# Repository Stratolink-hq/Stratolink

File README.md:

[stratolink.org](https://stratolink.org)

An open source pico balloon network. This repository contains the payload hardware, firmware, website, and flight models. Follow the [docs](https://stratolink.org/docs/getting-started) to build a payload, prepare a balloon, and register it on the [dashboard](https://stratolink.org/dashboard).

## Repository

```text
hardware/    KiCad schematics, PCB layouts, component libraries, and assembly files
firmware/    STM32WLE5 firmware, PlatformIO configuration, and host tests
web/         Website, public docs, dashboard, APIs, and forecast worker
supabase/    Database migrations and permission checks
simulation/  Balloon trajectories, buoyancy, and fleet coverage models
analysis/    Antenna, radio, power, and flight studies; bench diagnostics
docs/        Engineering notes for flight qualification and forecasting
scripts/     Sticker layout tool
assets/      Original project artwork and simulation media
```

## Firmware

Install [PlatformIO](https://platformio.org/install/cli). From the repository root:

```sh
cd firmware
cp include/secrets.h.example include/secrets.h
```

Fill in your regional TTN credentials, then build the flight environment:

```sh
pio run -e stratolink
```

Upload through J-Link over SWD:

```sh
pio run -e stratolink --target upload
```

Use the firmware revision that matches your board. [Hardware setup](https://stratolink.org/docs/hardware) covers assembly and programming; [firmware/README.md](firmware/README.md) covers configuration and host checks.

## Website

Use Node 22. From the repository root:

```sh
cd web
cp .env.example .env.local
ONNXRUNTIME_NODE_INSTALL=skip npm ci
npm run dev
```

Set the values in `.env.local` as described in [web/README.md](web/README.md). Run `npm run verify` before submitting website changes. Deployment and backend setup are documented there.

---

- [Fork this repository](https://github.com/Stratolink-hq/Stratolink/fork)
- [Watch this repo](https://github.com/Stratolink-hq/Stratolink/subscription)
- [Create issue](https://github.com/Stratolink-hq/Stratolink/issues/new)

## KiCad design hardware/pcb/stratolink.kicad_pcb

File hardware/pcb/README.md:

# Stratolink hardware v1.1 pilot

Current status, 8 November 2026: **corrected pilot layout verified; replacement cart saved and reviewed**. The cart contains PCB **Y28-2680969A** and PCBA **SMT026110862453-2680969A**, with all 57 fitted identities, sides and selection checkboxes verified. No replacement order has been submitted or paid, and manufacturing has not been approved. Cancellation of Y27-2680969A / SMT026110264457_Y27 remains requested but unconfirmed. See the [replacement review](../../analysis/v1_1_resubmit_20261108/README.md). The circuit remains unchanged. Layout changes are local clearance corrections; R1 procurement metadata is also updated in the PCB and schematic.

Open [stratolink.kicad_pro](stratolink.kicad_pro) in KiCad 10. The canonical project lives in `hardware/pcb` on `alpha/hardware-v1.1`; Git retains the flown v1. Keep `lib/`, `3d/`, `sym-lib-table` and `fp-lib-table` together. Board-specific footprints retain reviewed pad geometry and mask/paste settings. Do not replace them wholesale with stock footprints. All 68 embedded footprints match their updated local library pad geometry and model attachments; all 63 model attachments resolve with the project assets and KiCad 10 standard models.

The pilot retains the **0.40 mm, two-layer board, ENIG, green solder mask on both faces, no silkscreen and tented ordinary vias**. It uses one radio, the existing GNSS/pressure/IMU parts and the flat rear capacitor. The plan is **five fabricated boards, three assembled**, followed by physical qualification before a larger batch. Source and output hashes belong to the [current review](../../analysis/v1_1_resubmit_20261108/README.md) and [manufacturing manifest](../gerbers/v1.1-resubmit-20261108/manifest.json); use matching files together.

## Current board and assembly

| Area | Configuration |
|---|---|
| GNSS | AE2 at **(59.38, 33.13) mm**, with the **48 mm wire upward** from the top-left feed. Retain the engineer's placement and reviewed ground reference. |
| LoRa | Straight enameled wire downward from AE1. Reference cuts from the feed: **82 mm at 915 MHz**, 86 mm at 868 MHz or 83 mm compromise. |
| Precision temperature | Corrected **TMP117AIYBGR C2871893** ball map at U5, address 0x48. Native placement is now 180°. |
| Microphone | MK1/R20/C13, their dedicated routing and acoustic opening removed; PB3/PB4 unused. |
| Solar mounting | Two **1.0 × 2.0 mm open unplated notches**, upper-bank GND lands on both faces, and separate lower **0.70 mm positive wire holes**. Panels stay parallel. |
| Suspension | **2.0 mm plated holes / 3.2 mm GND rings**, for the triangular string bridle. |
| Programming | J3/J4 ordinary PTH contacts: 1 mm pitch, 0.50 mm holes, 0.88 mm front lands, **1.20 × 0.88 mm rear lands** offset 0.12 mm inward. No castellations. |
| Capacitor | C5 remains the flat hand-fitted rear part, now at **(64.875, 66.007) mm**, native 180°. Its enlarged courtyard is retained in the library. |
| Cell balancing | U8 **TLV8801DBVT** and R24/R25/R26/C22 retained. U8 is now on the **front at native 180°**. |
| Mask | U1 perimeter lands use native **+0.04 mm** mask expansion; U4 and L2 use **+0.05 mm**. Copper and paste geometry are preserved. |

The [mechanical review](../../analysis/v1_1_engineer_review_20261015/mechanics/README.md) includes full assembly, front and rear native renders. The nominal GNSS wire clears the modeled solar assembly by **20.54 mm**. A triangular bridle can cross its XY projection, so keep the actual string behind the wire with space for motion. C5's maximum case clears the board edge by **2.306 mm**, AE1's rear copper land by **0.696 mm** and the nearest Tag-Connect hole by **0.920 mm**. These distances exclude hand-placement error, solder and insulation. The solar film bend, terminal thickness and wire diameter remain nominal model assumptions.

## UV circuit and pilot population

U6 is **ams AS7331-AQFM C20482877**, with separate UVA/UVB/UVC channels, 3.3 V supplies and I²C address **0x74**. C14 and C23 are **100 nF CL05B104KO5NNNC C1525**. R27 is **3.3 MΩ, ±0.1%, ±25 ppm/K MCU0805MD3304BP500 C4313228**. READY is unconnected; SYN and the address inputs are grounded for polled command-mode operation. Current positions and orientations are recorded in the native board and generated placement files, replacing earlier placement notes.

The native design contains the complete circuit. Initial automated assembly **omits U6 only**, retaining **C14, C23 and R27**. Its BOM/CPL omit U6, and its stencil removes exactly the **16 U6 paste apertures**. Full-design paste remains separate for a later reviewed population. U6 is drawn in the full assembly renders but is absent from the three pilot assemblies. [Circuit and sourcing record](../../analysis/v1_1_release_20261012/as7331/README.md).

Build **`platformio run -e stratolink_v1_1_uv_dnp`** from `firmware/` for these pilots. It leaves PB3/PB4 quiet, makes no optical I²C requests and reports UV/lux unavailable. The older `stratolink_v1_1` target expects LTR390. A populated AS7331 has **no supported flight target yet** and requires its own validated driver, power-down behavior and raw multiband telemetry. [Firmware verification](../../analysis/v1_1_release_20261012/as7331/firmware/README.md).

AS7331 supports an experimental estimate of the **ozone column above the balloon**, not calibrated concentration directly. It has no visible-light ALS channel. Its −40…85 °C operating range needs actual die-temperature verification. The manufacturer recommends incidence within ±10° and warns that visible/IR leakage can overwhelm weak UV signals. Angle control, spectral filtering, calibration and low-pressure/thermal qualification remain necessary. U6-absent pilots produce no UV or ozone data. [Primary-source requirements](../../analysis/v1_1_release_20261012/as7331/review/requirements.md).

## Electrical identities and qualification

U5's map is **A1 SDA, A2 SCL, B1 +3.3 V, B2 GND, C1 GND, C2 grounded ALERT**. The AI grade is specified to ±0.2 °C over −40…100 °C and ±0.25 °C over −55…125 °C under its stated conditions. Sunlight and board conduction add ambient-air error. Exact retained identities include **RAK3172-8-SM-NI C5452091** at U2, **RC0402FR-073M65L C477700** at R4 and **PESD5V0U1BB C5272735** at D1/D3. [Identity review](../../analysis/v1_1_release_20261012/identities/README.md).

R1 is **7.50 MΩ UNI-ROYAL 0402WGF7504TCE C423135**, with R2 at 4.22 MΩ, for a nominal **5.041 V** charge ceiling. The stock-driven substitution preserves ±1% tolerance, ±100 ppm/K, 50 V, 62.5 mW and the −55…155 °C operating range, with no footprint or routing change. See the [R1 sourcing review](../../analysis/v1_1_resubmit_20261108/r1-sourcing.md). C5 is **DMF4B5R5G105M3DTA0**: pad 1 positive, pad 2 negative, pad 3 **SC_MID**, not ground. U8 feedback joins the output to its inverting input **before R26**; R26 connects to the midpoint. R24/R25 are 4.75 MΩ, R26 is 22 Ω and C22 is 100 nF. C5 is fitted after reflow and cleaning using its secondary soldering process. [Power circuit review](../../analysis/v1_1_release_20261012/power/README.md).

Charge plateau, both cell voltages, midpoint stability, cold leakage/ESR, dark current and sunrise recovery require measurement. **Cold panel Voc/current and BQ25570 input-voltage/input-power limits remain unresolved physical bounds.** CAD cannot qualify them.

The SWD mapping remains the standard RAK3172 mapping. Use a receive-only adapter for passive J4 UART observation; an adapter transmitter can contend with the GNSS transmitter. Keep the 4.7 kΩ I²C pull-ups pending a measured 300 ns rise-time check. C8/C21 remain. [Digital review](../../analysis/v1_1_peer_review_20261014/digital/README.md), [bypass review](../../analysis/v1_1_peer_review_20261014/power/README.md).

## Manufacturing review

Enabled checks use the reviewed **0.10 mm copper process floor, 0.15 mm general clearance target and 0.20 mm ordinary routed-edge minimum**, with named fine-pitch/contact exceptions. The two intended ERC exclusions are U5 grounded ALERT and U7 SA0. Actual mask Gerbers for the repaired U1/U4/L2 apertures meet **0.09 mm aperture-to-foreign-copper** and **0.10 mm mask-web** checks. Solar polarity symbols are copper with mask openings; native silkscreen artwork count is zero. These checks do not establish controlled impedance, measured RF gain or factory CAM approval.

The package contains **58 full-design / 57 pilot automatic-assembly references**, **30 pilot part groups** and **11 manual/DNP exclusions**. J1/J2/J20 lost their exclude-position flags in the incoming board. The final PCB and schematic restore them; the generator also retains explicit manual exclusions. [BOM, CPL and fabrication package](../gerbers/v1.1-resubmit-20261108/README.md).

**The replacement cart preview has been reviewed; its later factory production files still require review.** The retained supplier CPL conventions are **U1 bottom 270°, U5 top 180° and U8 top 90°**. In a north-up, bottom-facing view, U1 pin 1 is **upper-left beside C4/L1** in the new preview, matching the corrected physical orientation. All seven fitted IC indices were checked. A CSV angle alone does not establish orientation. U6 is omitted. See the [replacement review](../../analysis/v1_1_resubmit_20261108/README.md).

The October packages and Y24/Y26 carts are historical. Y27's PCB production file was approved November 6, but the later assembly review found the body-clearance problem. That approval does not authorize the replacement. Use its new BOM, CPL and Gerbers together and review JLC's new manufacturing and placement files.
- [Fabrication and manual assembly instructions](FABRICATION.md)
- [v1.1 / v2 checklist](TODO.md)
- [Current replacement review and change ledger](../../analysis/v1_1_resubmit_20261108/README.md)
- [October engineer reroute baseline](../../analysis/v1_1_engineer_review_20261015/README.md)
- [Pilot acceptance procedure](../../analysis/v1_1_release_20261012/pilot-acceptance.md)
- [Solar 3D model assumptions](3d/solar/README.md)

Historical analysis files retain earlier placements and supplier previews. Use the current review and package manifest to identify this board.

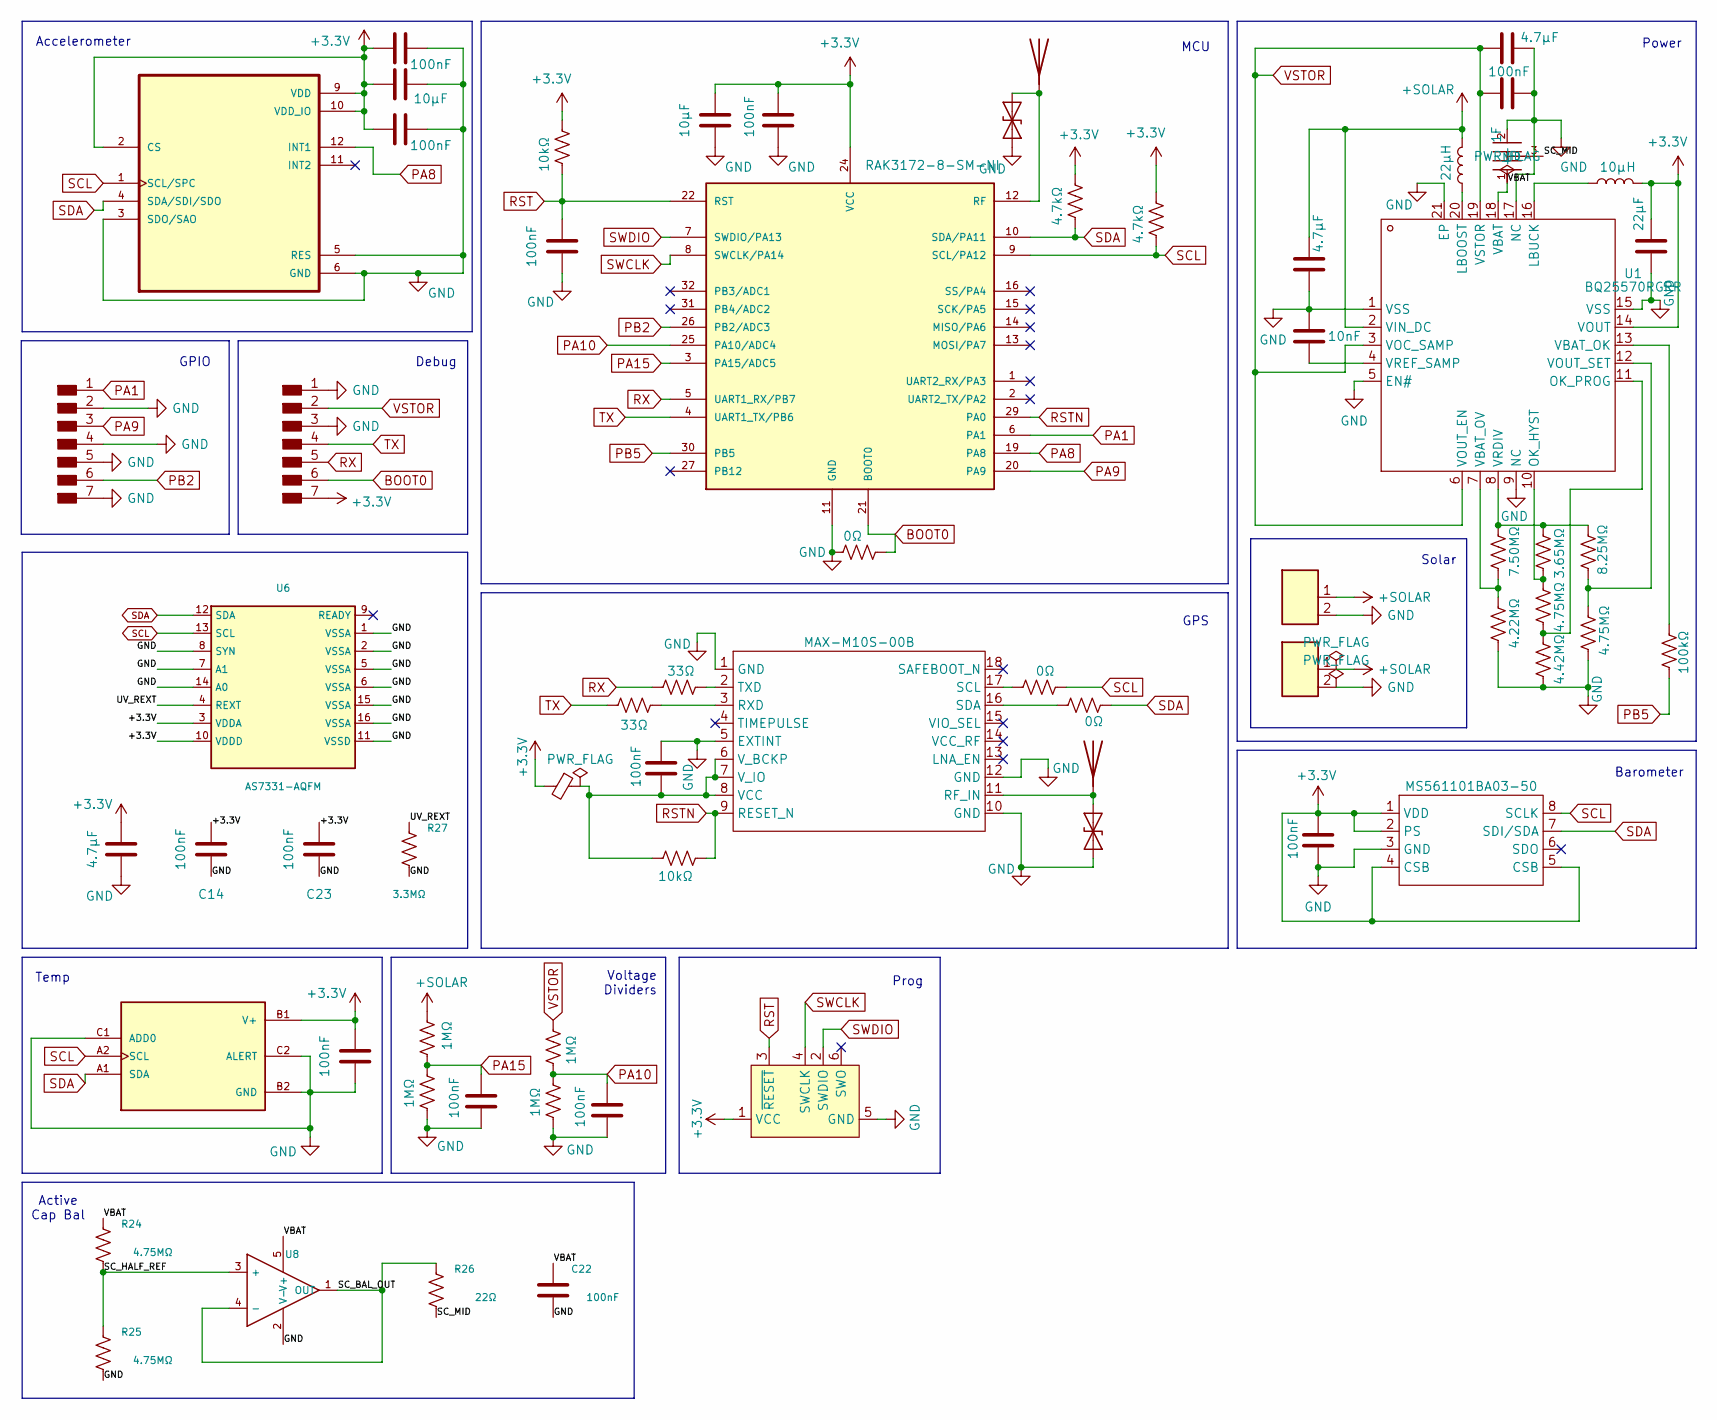
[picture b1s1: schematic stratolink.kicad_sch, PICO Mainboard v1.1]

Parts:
AE1: Enameled Cu wire 82mm (915MHz reference); Stratolink_LoRa_Wire_PTH_D1p0
AE2: Enameled Cu wire 48mm (GNSS L1); Stratolink_GNSS_Wire_PTH_D1p0
C1: 10nF; Stratolink_v1p1_C1_C_0402_1005Metric; Manufacturer_Part_Number GRM1555C1E103JE01D; LCSC C3855387
C2: 4.7μF; Stratolink_v1p1_C2_C_0603_1608Metric; Manufacturer_Part_Number CL10A475KP8NNNC; LCSC C1705
C3: 4.7μF; Stratolink_v1p1_C3_C_0603_1608Metric; Manufacturer_Part_Number CL10A475KP8NNNC; LCSC C1705
C4: 100nF; Stratolink_v1p1_C4_C_0402_1005Metric; Manufacturer_Part_Number CL05B104KO5NNNC; LCSC C1525
C5: 1F; Stratolink_v1p1_C5_DMF4B5R5G105M3DTA0; Manufacturer_Part_Number DMF4B5R5G105M3DTA0
C6: 22µF; Stratolink_v1p1_C6_C_0805_2012Metric; Manufacturer_Part_Number CL21A226MAYNNNE; LCSC C602037
C7: 100nF; Stratolink_v1p1_C7_C_0402_1005Metric; Manufacturer_Part_Number CL05B104KO5NNNC; LCSC C1525
C8: 10μF; Stratolink_v1p1_C8_C_0603_1608Metric; Manufacturer_Part_Number CL10A106KP8NNNC; LCSC C19702
C9: 100nF; Stratolink_v1p1_C9_C_0402_1005Metric; Manufacturer_Part_Number CL05B104KO5NNNC; LCSC C1525
C10: 100nF; Stratolink_v1p1_C10_C_0402_1005Metric; Manufacturer_Part_Number CL05B104KO5NNNC; LCSC C1525
C11: 100nF; Stratolink_v1p1_C11_C_0402_1005Metric; Manufacturer_Part_Number CL05B104KO5NNNC; LCSC C1525
C12: 100nF; Stratolink_v1p1_C12_C_0402_1005Metric; Manufacturer_Part_Number CL05B104KO5NNNC; LCSC C1525
C14: 100nF; Stratolink_v1p1_C14_C_0402_1005Metric; Manufacturer_Part_Number CL05B104KO5NNNC; LCSC C1525
C15: 100nF; Stratolink_v1p1_C15_C_0402_1005Metric; Manufacturer_Part_Number CL05B104KO5NNNC; LCSC C1525
C16: 4.7μF; Stratolink_v1p1_C16_C_0603_1608Metric; Manufacturer_Part_Number CL10A475KP8NNNC; LCSC C1705
C17: 100nF; Stratolink_v1p1_C17_C_0402_1005Metric; Manufacturer_Part_Number CL05B104KO5NNNC; LCSC C1525
C19: 100nF; Stratolink_v1p1_C19_C_0402_1005Metric; Manufacturer_Part_Number CL05B104KO5NNNC; LCSC C1525
C20: 100nF; Stratolink_v1p1_C20_C_0402_1005Metric; Manufacturer_Part_Number CL05B104KO5NNNC; LCSC C1525
C21: 10μF; Stratolink_v1p1_C21_C_0603_1608Metric; Manufacturer_Part_Number CL10A106KP8NNNC; LCSC C19702
C22: 100nF; Stratolink_v1p1_C22_C_0402_1005Metric; MPN CL05B104KO5NNNC; LCSC Part # C1525
C23: 100nF; Stratolink_v1p1_C23_C_0402_1005Metric; Manufacturer_Part_Number CL05B104KO5NNNC; LCSC C1525
D1: PESD5V0U1BB; Stratolink_v1p1_D1_D_SOD-523; Manufacturer_Part_Number PESD5V0U1BB; LCSC C5272735
D3: PESD5V0U1BB; Stratolink_v1p1_D3_D_SOD-523; Manufacturer_Part_Number PESD5V0U1BB; LCSC C5272735
FB1: BLM15AG601SN1D; Stratolink_v1p1_FB1_C_0402_1005Metric; Manufacturer_Part_Number BLM15AG601SN1D; LCSC C76884
J1: Solar panel direct solder; Solar_Notch_Right_1p0x2p0
J2: Solar panel direct solder; Solar_Notch_Left_1p0x2p0
J3: Programming_1x07_P1.00mm_D0.50mm; Stratolink_Programming_Left_1x07_P1p00_D0p50_BackTack1p20x0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
J4: Programming_1x07_P1.00mm_D0.50mm; Stratolink_v1p1_J4_Stratolink_Programming_Right_1x07_P1p00_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
J20: Conn_ARM_SWD_TagConnect_TC2030-NL; Stratolink_v1p1_J20_Tag-Connect_TC2030-IDC-NL_2x03_P1.27mm_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
L1: 22µH; Stratolink_v1p1_L1_IND_LPS4018-223MRC; Manufacturer_Part_Number LPS4018-223MRC; LCSC C5278935
L2: 10µH; INDC1608X90N; Manufacturer_Part_Number PWCWAQ1608F-100KTT; LCSC C436784
R1: 7.50MΩ; Stratolink_v1p1_R1_R_0402_1005Metric; Manufacturer_Part_Number 0402WGF7504TCE; LCSC C423135
R2: 4.22MΩ; Stratolink_v1p1_R2_R_0402_1005Metric; Manufacturer_Part_Number CRCW04024M22FKED; LCSC C2091474
R3: 4.75MΩ; Stratolink_v1p1_R3_R_0402_1005Metric; Manufacturer_Part_Number FRC0402F4754TS; LCSC C2998153
R4: 3.65MΩ; Stratolink_v1p1_R4_R_0402_1005Metric; Manufacturer_Part_Number RC0402FR-073M65L; LCSC C477700
R5: 4.42MΩ; Stratolink_v1p1_R5_R_0402_1005Metric; Manufacturer_Part_Number GR0402F4M42TAG00; LCSC C49654874
R6: 8.25MΩ; Stratolink_v1p1_R6_R_0402_1005Metric; Manufacturer_Part_Number 0402WGF8254TCE; LCSC C423131
R7: 4.75MΩ; Stratolink_v1p1_R7_R_0402_1005Metric; Manufacturer_Part_Number FRC0402F4754TS; LCSC C2998153
R8: 100kΩ; Stratolink_v1p1_R8_R_0402_1005Metric; Manufacturer_Part_Number RC0402FR-07100KL; LCSC C60491
R9: 0Ω; Stratolink_v1p1_R9_R_0402_1005Metric; Manufacturer_Part_Number RC0402FR-070RL; LCSC C106231
R10: 10kΩ; Stratolink_v1p1_R10_R_0402_1005Metric; Manufacturer_Part_Number RC0402FR-0710KL; LCSC C60490
R11: 4.7kΩ; Stratolink_v1p1_R11_R_0402_1005Metric; Manufacturer_Part_Number RC0402FR-074K7L; LCSC C105871
R12: 4.7kΩ; Stratolink_v1p1_R12_R_0402_1005Metric; Manufacturer_Part_Number RC0402FR-074K7L; LCSC C105871
R13: 0Ω; Stratolink_v1p1_R13_R_0402_1005Metric; Manufacturer_Part_Number RC0402FR-070RL; LCSC C106231
R14: 0Ω; Stratolink_v1p1_R14_R_0402_1005Metric; Manufacturer_Part_Number RC0402FR-070RL; LCSC C106231
R15: 33Ω; Stratolink_v1p1_R15_R_0402_1005Metric; Manufacturer_Part_Number RC0402FR-0733RL; LCSC C138002
R16: 33Ω; Stratolink_v1p1_R16_R_0402_1005Metric; Manufacturer_Part_Number RC0402FR-0733RL; LCSC C138002
R18: 10kΩ; Stratolink_v1p1_R18_R_0402_1005Metric; Manufacturer_Part_Number RC0402FR-0710KL; LCSC C60490
R19: 1MΩ; Stratolink_v1p1_R19_R_0402_1005Metric; Manufacturer_Part_Number RC0402FR-071ML; LCSC C138033
R21: 1MΩ; Stratolink_v1p1_R21_R_0402_1005Metric; Manufacturer_Part_Number RC0402FR-071ML; LCSC C138033
R22: 1MΩ; Stratolink_v1p1_R22_R_0402_1005Metric; Manufacturer_Part_Number RC0402FR-071ML; LCSC C138033
R23: 1MΩ; Stratolink_v1p1_R23_R_0402_1005Metric; Manufacturer_Part_Number RC0402FR-071ML; LCSC C138033
R24: 4.75MΩ; Stratolink_v1p1_R24_R_0402_1005Metric; MPN FRC0402F4754TS; LCSC Part # C2998153
R25: 4.75MΩ; Stratolink_v1p1_R25_R_0402_1005Metric; MPN FRC0402F4754TS; LCSC Part # C2998153
R26: 22Ω; Stratolink_v1p1_R26_R_0402_1005Metric; MPN 0402WGF220JTCE; LCSC Part # C25092
R27: 3.3MΩ; Stratolink_v1p1_R27_R_0805_2012Metric; MPN MCU0805MD3304BP500; LCSC Part # C4313228
U1: BQ25570RGRR; Stratolink_v1p1_U1_QFN50P350X350X100-21N; Manufacturer Part BQ25570RGRR; LCSC Part Name 适用于能量收集器供电应用的微功率升压充电器与降压转换器
U2: RAK3172-8-SM-NI; Stratolink_v1p1_U2_RAK3172; Manufacturer_Part_Number RAK3172-8-SM-NI; LCSC C5452091
U3: MAX-M10S-00B; Stratolink_v1p1_U3_XCVR_MAX-M10S-00B; Manufacturer Part MAX-M10S-00B; LCSC Part Name MAX-M10S-00B
U4: MS561101BA03-50; Stratolink_v1p1_U4_SON125P500X300X100-8N; Manufacturer Part MS561101BA03-50; LCSC Part Name MS561101BA03-50
U5: TMP117AIYBGR; Stratolink_v1p1_U5_BGA6N40P3X2_148X95X53; PARTREV D; LCSC C2871893
U6: AS7331-AQFM; Stratolink_v1p1_U6_AS7331_OLGA16; Manufacturer_Part_Number AS7331-AQFM; LCSC C20482877
U7: LIS2DH12TR; Stratolink_v1p1_U7_PQFN50P200X200100-12N; Manufacturer_Part_Number LIS2DH12TR; LCSC C110926
U8: TLV8801DBVT; Stratolink_v1p1_U8_SOT-23-5; MPN TLV8801DBVT; LCSC Part # C544879

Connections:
+3.3V: C6.2, C7.2, C8.2, C11.2, C12.2, C14.2, C16.2, C19.2, C20.2, C21.2, C23.2, FB1.2, J4.7, J20.1 (VCC), L2.2, R10.1, R11.1, R12.1, U1.14 (VOUT), U2.24 (VCC), U4.1 (VDD), U4.2 (PS), U4.4 (CSB), U4.5 (CSB), U5.B1 (V+), U6.3 (VDDA), U6.10 (VDDD), U7.2 (CS), U7.9 (VDD), U7.10 (VDD_IO)
+SOLAR: C2.1, J1.1, J2.1, L1.2, R19.1, U1.2 (VIN_DC)
/SC_BAL_OUT: R26.1, U8.1 (OUT), U8.4 (-)
/SC_HALF_REF: R24.2, R25.1, U8.3 (+)
/SC_MID: C5.3 (MID), R26.2
/UV_REXT: R27.1, U6.4 (REXT)
/VBAT: C5.1 (+), C22.1, R24.1, U1.18 (VBAT), U8.5 (V+)
BOOT0: J4.6, R9.2, U2.21 (BOOT0)
GND: C1.1, C2.2, C3.2, C4.2, C5.2 (-), C6.1, C7.1, C8.1, C9.1, C10.2, C11.1, C12.1, C14.1, C15.1, C16.1, C17.1, C19.1, C20.1, C21.1, C22.2, C23.1, D1.1 (A1), D3.1 (A1), J1.2, J2.2, J3.2, J3.4, J3.5, J3.7, J4.1, J4.3, J20.5 (GND), R2.2, R5.2, R7.2, R9.1, R21.2, R23.2, R25.2, R27.2, U1.1 (VSS), U1.5 (EN#), U1.9 (NC), U1.15 (VSS), U1.17 (NC), U1.21 (EP), U2.11 (GND), U2.17 (GND), U2.18 (GND), U2.23 (GND), U2.28 (GND), U3.1 (GND), U3.5 (EXTINT), U3.10 (GND), U3.12 (GND), U4.3 (GND), U5.B2 (GND), U5.C1 (ADD0), U5.C2 (ALERT), U6.1 (VSSA), U6.2 (VSSA), U6.5 (VSSA), U6.6 (VSSA), U6.7 (A1), U6.8 (SYN), U6.11 (VSSD), U6.14 (A0), U6.15 (VSSA), U6.16 (VSSA), U7.3 (SDO/SAO), U7.5 (RES), U7.6 (GND), U7.7 (GND), U7.8 (GND), U8.2 (V-); also elsewhere on the board
unnamed: AE1.1 (A_1), D1.2 (A2), U2.12 (RF)
unnamed: AE2.1 (A_1), D3.2 (A2), U3.11 (RF_IN)
unnamed: L1.1, U1.20 (LBOOST)
unnamed: L2.1, U1.16 (LBUCK)
unnamed: R3.1, R4.2, U1.10 (OK_HYST)
unnamed: R3.2, R5.1, U1.11 (OK_PROG)
unnamed: R8.1, U1.13 (VBAT_OK)
unnamed: R1.2, R2.1, U1.7 (VBAT_OV)
unnamed: R6.2, R7.1, U1.12 (VOUT_SET)
unnamed: R1.1, R4.1, R6.1, U1.8 (VRDIV)
unnamed: C1.2, U1.4 (VREF_SAMP)
unnamed: R16.2, U3.3 (RXD)
unnamed: R13.1, U3.17 (SCL)
unnamed: R14.1, U3.16 (SDA)
unnamed: R15.2, U3.2 (TXD)
unnamed: C10.1, FB1.1, R18.1, U3.6 (V_BCKP), U3.7 (V_IO), U3.8 (VCC)
PA1: J3.1, U2.6 (PA1)
PA8: U2.19 (PA8), U7.12 (INT1)
PA9: J3.3, U2.20 (PA9)
PA10: C17.2, R22.2, R23.1, U2.25 (PA10/ADC4)
PA15: C15.2, R19.2, R21.1, U2.3 (PA15/ADC5)
PB2: J3.6, U2.26 (PB2/ADC3)
PB5: R8.2, U2.30 (PB5)
RST: C9.2, J20.3 (~RESET), R10.2, U2.22 (RST)
RSTN: R18.2, U2.29 (PA0), U3.9 (RESET_N)
RX: J4.5, R15.1, U2.5 (UART1_RX/PB7)
SCL: R12.2, R13.2, U2.9 (SCL/PA12), U4.8 (SCLK), U5.A2 (SCL), U6.13 (SCL), U7.1 (SCL/SPC)
SDA: R11.2, R14.2, U2.10 (SDA/PA11), U4.7 (SDI/SDA), U5.A1 (SDA), U6.12 (SDA), U7.4 (SDA/SDI/SDO)
SWCLK: J20.4 (SWCLK), U2.8 (SWCLK/PA14)
SWDIO: J20.2 (SWDIO), U2.7 (SWDIO/PA13)
TX: J4.4, R16.1, U2.4 (UART1_TX/PB6)
VSTOR: C3.1, C4.1, J4.2, R22.1, U1.3 (VOC_SAMP), U1.6 (VOUT_EN), U1.19 (VSTOR)

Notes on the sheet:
GPS
Active Cap Bal
Prog
Solar
MCU
Debug
Power
Barometer
GPIO
Temp
Voltage Dividers
Accelerometer

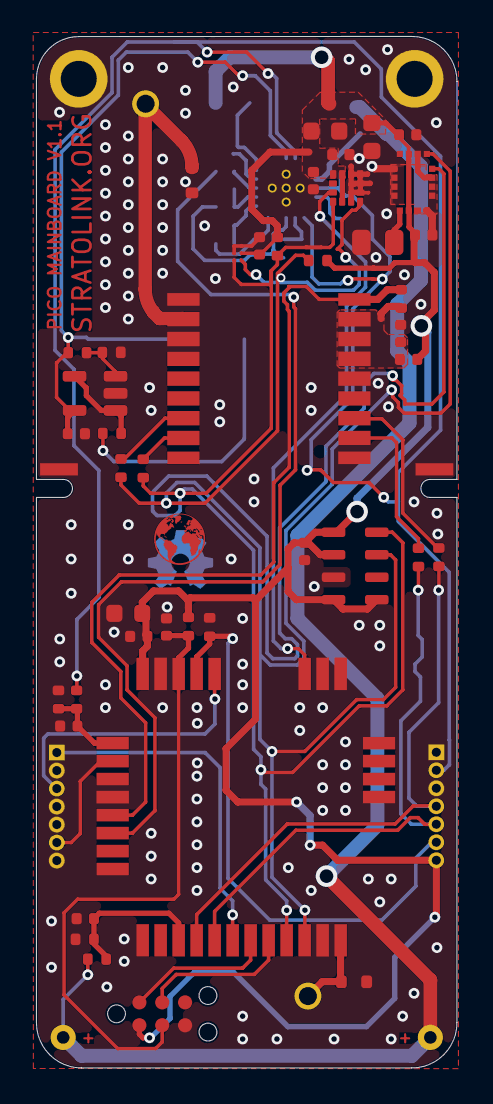
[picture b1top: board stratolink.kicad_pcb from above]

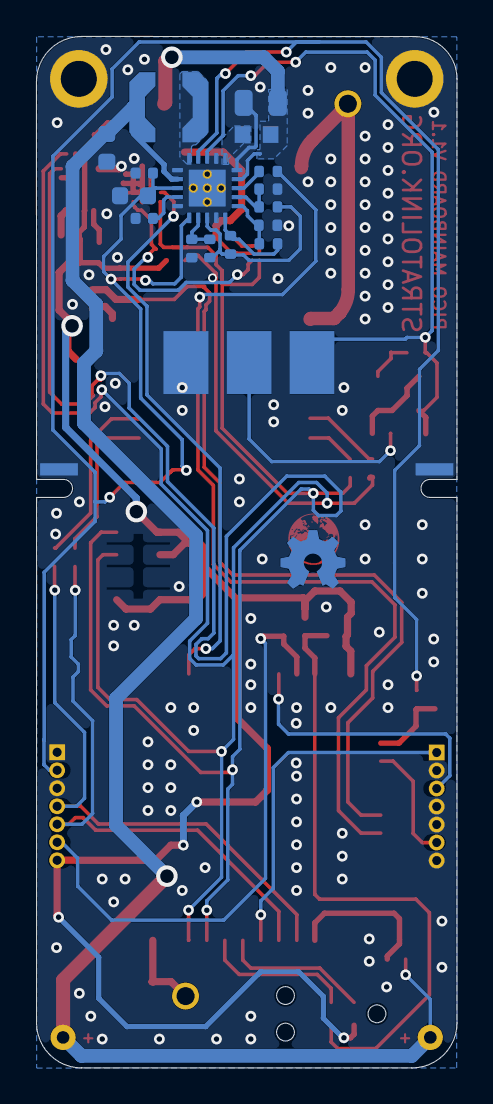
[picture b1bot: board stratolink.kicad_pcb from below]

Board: 2 copper layers, 23.4 x 57.3 mm, 68 parts (17 on the bottom side), 41 nets.

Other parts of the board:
H1, H2: Suspension 2.0 mm PTH; Suspension_PTH_D2p0_OD3p2

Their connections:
GND: H1.1, H2.1; also elsewhere on the board
